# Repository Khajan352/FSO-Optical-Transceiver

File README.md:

# Free-Space Optical Transceiver

A line-of-sight optical link that carries audio and live sensor data over a
laser beam, with no wire and no radio. Transmitter modulates a laser diode;
receiver recovers the signal through a photodiode front end and an op-amp
gain stage.

**Status:** Built on solder board and bench tested.
**Tools:** LTspice, Autodesk Eagle, Arduino, Falstad

## Specification

| Parameter | Value |
|---|---|
| Channel | Free-space optical, line of sight |
| Source | Red laser diode, two channels |
| Detector | BPW46 photodiode front end plus IR phototransistor |
| Receiver gain stage | LM358 dual op-amp |
| Payload | Analogue audio, and digital sensor data over serial |
| Supply | 9 V per side, battery powered |
| Alignment | Servo-mounted head on an adjustable clamp |

## What is in this repository

| Path | Contents |
|---|---|
| `simulation/transceiver.asc` | Transmitter and receiver chain, LTspice |
| `simulation/receiver-stage-draft.asc` | Earlier receiver stage |
| `simulation/transmitter-falstad.txt` | Transmitter netlist, Falstad format |
| `hardware/transceiver.sch` | Eagle schematic |
| `hardware/transceiver.brd` | Eagle board layout |
| `hardware/bom.csv` | Bill of materials as built |
| `firmware/transmitter.ino` | Sensor acquisition and transmit side |
| `firmware/receiver.ino` | Receive and decode side |
| `images/` | Photographs from a related build, see below |

## How it works

The link has two independent paths sharing the same optics.

**Audio path.** Line-level audio enters through a 3.5 mm jack, is buffered
and used to modulate laser intensity directly. At the far end the photodiode
current is converted to a voltage and amplified back up to line level into a
second 3.5 mm jack. This path is fully analogue, so there is no sample rate
and no codec, and the bandwidth limit is set by the detector and the amplifier
rather than by any digital stage.

**Data path.** The transmitter microcontroller reads a DHT11 for temperature
and humidity, a soil moisture probe, and an infrared sensor used to count
objects passing a point, then sends framed messages over serial into the same
optical channel. The receiver decodes them back to serial at the other end.
This is what demonstrates the link is carrying real information rather than
just a tone.

Two 10 kΩ potentiometers set transmit drive and receive gain, so the link can
be trimmed for distance and ambient light rather than being fixed at design
time. A servo on an adjustable clamp handles alignment, which matters because
a laser link has a very narrow acceptance angle and a few degrees of drift
breaks it.

## Simulation

`simulation/transceiver.asc` models the full chain: a 3.3 V, 100 Hz input
standing in for the modulating signal, an op-amp transmit stage, an
optocoupler standing in for the optical hop itself, and two receive gain
stages on a 9 V rail. Feedback and bias networks are 10 kΩ throughout with a
5.1 kΩ setting the final stage.

The simulation uses OP747 op-amps because that is what had a usable SPICE
model to hand. The board was built with LM358, which is what the bill of
materials lists. The two parts are pin compatible in this configuration and
the topology is unchanged, but the simulated slew rate and input offset are
not the ones on the bench, so the simulation shows the intended behaviour of
the circuit rather than the measured behaviour of the build.

The transmitter was first roughed out in Falstad before moving to LTspice;
that netlist is kept in `simulation/transmitter-falstad.txt`.

## Design notes

**Why a photodiode front end and not just a phototransistor.** A
phototransistor gives gain for free but is slow and its response varies
widely part to part. The BPW46 photodiode is fast and linear, at the cost of
producing a very small current that has to be amplified. Both are in the
build: the photodiode carries the signal path, the phototransistor is used
where speed does not matter.

**Why the receiver is two stages.** A single stage with enough gain to bring
photodiode current up to line level would sit close to the op-amp's
gain-bandwidth limit and would amplify its own offset along with the signal.
Splitting it lets the first stage do current-to-voltage conversion close to
the detector and the second stage set the output level.

**Ambient light is the real enemy.** Room lighting puts a large DC term and a
mains-frequency component on top of the signal. The gain trim exists so the
front end can be backed off far enough not to saturate under whatever
lighting the link is being demonstrated in.

## Bill of materials

See [`hardware/bom.csv`](hardware/bom.csv). Headline parts:

| Part | Component |
|---|---|
| LM358ANFS-ND | Dual op-amp, receiver gain stages |
| BPW46 | Photodiode, optical front end |
| LT9593-91-0125 | IR phototransistor |
| 2N3904 | NPN transistor |
| hs-244 | Servo motor, beam alignment |
| 3386F-103-ND | 10 kΩ potentiometers, drive and gain trim |

## Related build

The photographs below are **not** of the boards this schematic describes.
They are from a separate optical link built on the same transmitter and
receiver topology: laser diode source, photodiode front end, LM358 gain
stage, Arduino either side carrying sensor data. They are included because
they show that topology working, not as evidence for this design.

Transmitter on the right with a DHT11 and an infrared sensor attached,
receiver on the left, beam crossing the gap between them into a second
Arduino.

Both ends on solder board. The op-amps sit in DIP sockets so they could be
swapped during bring-up, a trimmer sets gain, and each side runs from its
own 9 V battery so there is no shared ground between transmitter and
receiver. Audio in and out through the 3.5 mm jacks.

The transmitter kept on breadboard while the drive circuit was still
changing, laser diode at the edge pointing down at the receiver. The red
bloom is the beam scattering off the board surface, which is also how
alignment was judged by eye.

## Licence

MIT. See [LICENSE](LICENSE).

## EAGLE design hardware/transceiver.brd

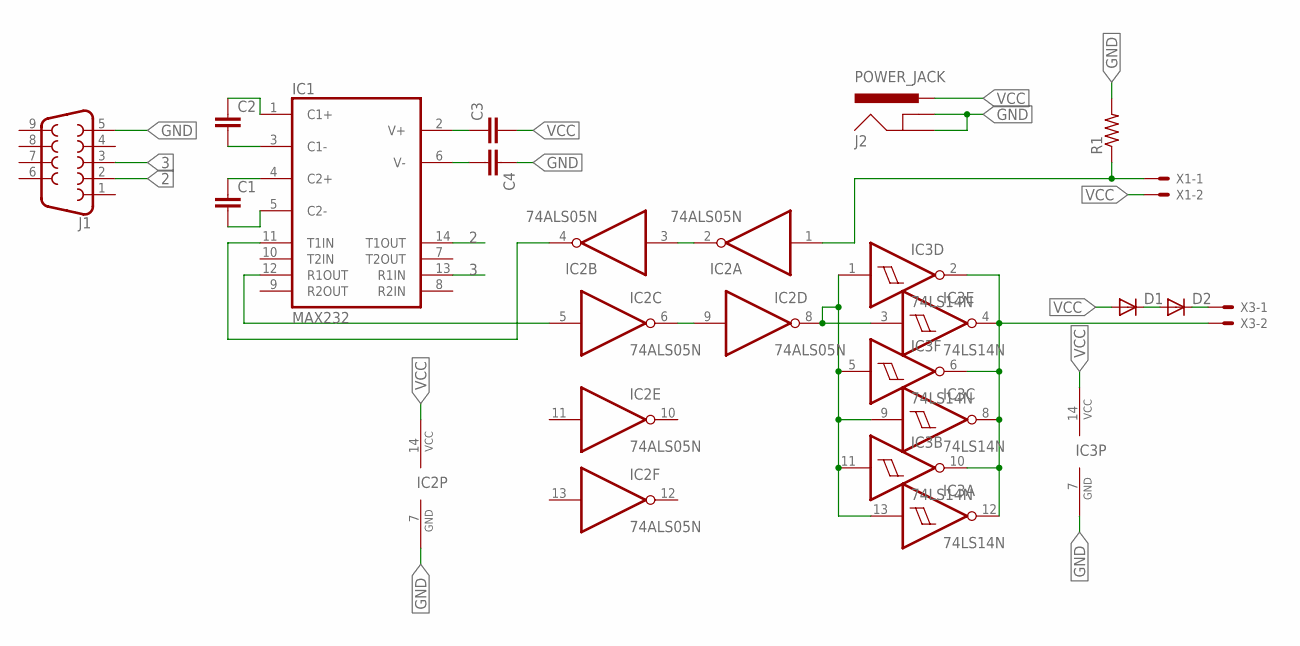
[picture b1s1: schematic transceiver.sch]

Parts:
C1, C2, C3, C4: C2,5-3; C2.5-3
D1, D2: 1N4004; DO41-10
IC1: MAX232; DIL16
IC2: 74ALS05N; DIL14
IC3: 74LS14N; DIL14
J1: DB9FEMALE; DB9
J2: POWER_JACK; POWER_JACK_PTH
R1: R-US_0207/12; 0207/12
X1, X3: JST-XH-02-PIN-LONG-PAD; JST-XH-02-PACKAGE-LONG-PAD

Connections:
2: IC1.14 (T1OUT), J1.2
3: IC1.13 (R1IN), J1.3
GND: C4.1, IC1.15 (GND), IC2.7 (GND), IC3.7 (GND), J1.5, J2.GND, J2.GNDBREAK, R1.2
unnamed: IC1.11 (T1IN), IC2.4 (O)
unnamed: IC1.12 (R1OUT), IC2.5 (I)
unnamed: IC2.2 (O), IC2.3 (I)
unnamed: IC2.6 (O), IC2.9 (I)
unnamed: IC2.1 (I), R1.1, X1.1
unnamed: C4.2, IC1.6 (V-)
unnamed: IC2.8 (O), IC3.1 (I), IC3.3 (I), IC3.5 (I), IC3.9 (I), IC3.11 (I), IC3.13 (I)
unnamed: C1.1, IC1.4 (C2+)
unnamed: C2.2, IC1.3 (C1-)
unnamed: C1.2, IC1.5 (C2-)
unnamed: C2.1, IC1.1 (C1+)
unnamed: C3.1, IC1.2 (V+)
unnamed: D1.C, D2.A
unnamed: IC3.2 (O), IC3.4 (O), IC3.6 (O), IC3.8 (O), IC3.10 (O), IC3.12 (O), X3.2
unnamed: D2.C, X3.1
VCC: C3.2, D1.A, IC1.16 (VCC), IC2.14 (VCC), IC3.14 (VCC), J2.PWR, X1.2

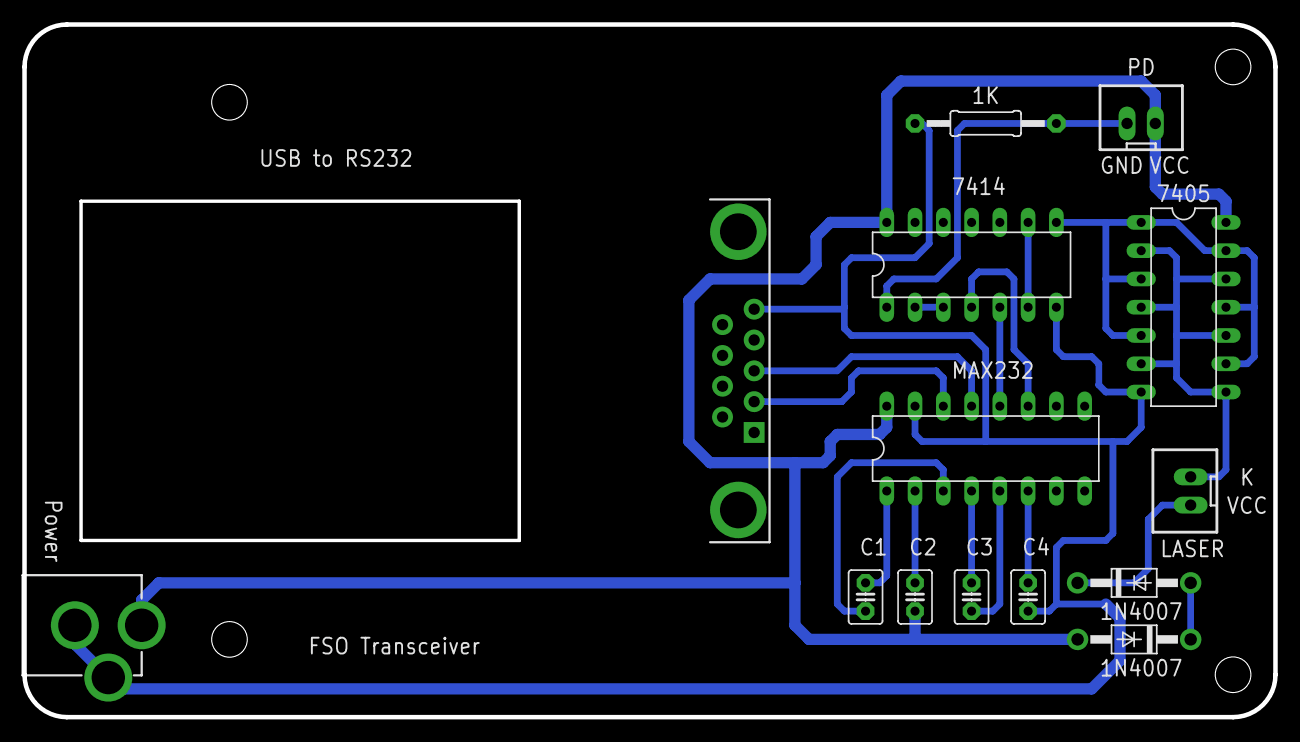
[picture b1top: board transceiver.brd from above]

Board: 2 copper layers, 112.4 x 62.2 mm, 14 parts (0 on the bottom side), 19 nets.

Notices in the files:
parts and their libraries:
SparkFun-Connectors: Licensing: Creative Commons ShareAlike 4.0 International - https://creativecommons.org/licenses/by-sa/4.0
